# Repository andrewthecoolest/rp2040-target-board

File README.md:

# RP2040 Target Board

A ChipWhisperer-compatible target board built around the Raspberry Pi RP2040.

## Overview

This board connects an RP2040 with shunt to the CW308 UFO.

## Features

- RP2040 dual-core Arm Cortex-M0+ microcontroller
- 16MB QSPI flash
- ChipWhisperer 60-pin UFO308 target connector
- 5Ω shunt (changable to anything < 10Ω)
- 2-layer PCB
- Made with love

## Ordering

If you want to make your own, Gerbers are in `fab/gerbers/`. I made it with JLCPCB default 2-layer settings, so I included CPL and BOM for JLCPCB. For JLCPCB specifically, I've already zipped the gerbers and drill.

## Repository Structure

```
├── hardware/
│   ├── rp2040-target.kicad_pro     KiCad project
│   ├── rp2040-target.kicad_pcb     PCB
│   ├── rp2040-target.kicad_sch     Main schematic
│   ├── rp2040-target.kicad_wks     AR template
│   ├── RP2040.kicad_sch            RP2040 sub-sheet
│   ├── Flash.kicad_sch             Flash sub-sheet
│   └── libs/
│       ├── Conn_UFO308.kicad_sym   UFO308 target schematic symbol
│       └── UFO308.pretty/          UFO308 target footprint
│
├── fab/
│   ├── gerbers/                    Gbrs and drill
│   ├── 2040-target-fab.zip         Gerber and drill zip
│   ├── jlcpcb_bom.csv              BOM
│   └── jlcpcb_cpl.csv              CPL
│
└── docs/
    ├── schematic.pdf
    └── images/
```

## Andrew Acknowledgement

Start Message.
    My name is Andrew ᶘ ◕ᴥ◕ᶅ
Conclude Message.

## License

Copyright Attack Research 2026. Licensed under the [CERN Open Hardware Licence Version 2 - Permissive (CERN-OHL-P v2)](LICENSE).

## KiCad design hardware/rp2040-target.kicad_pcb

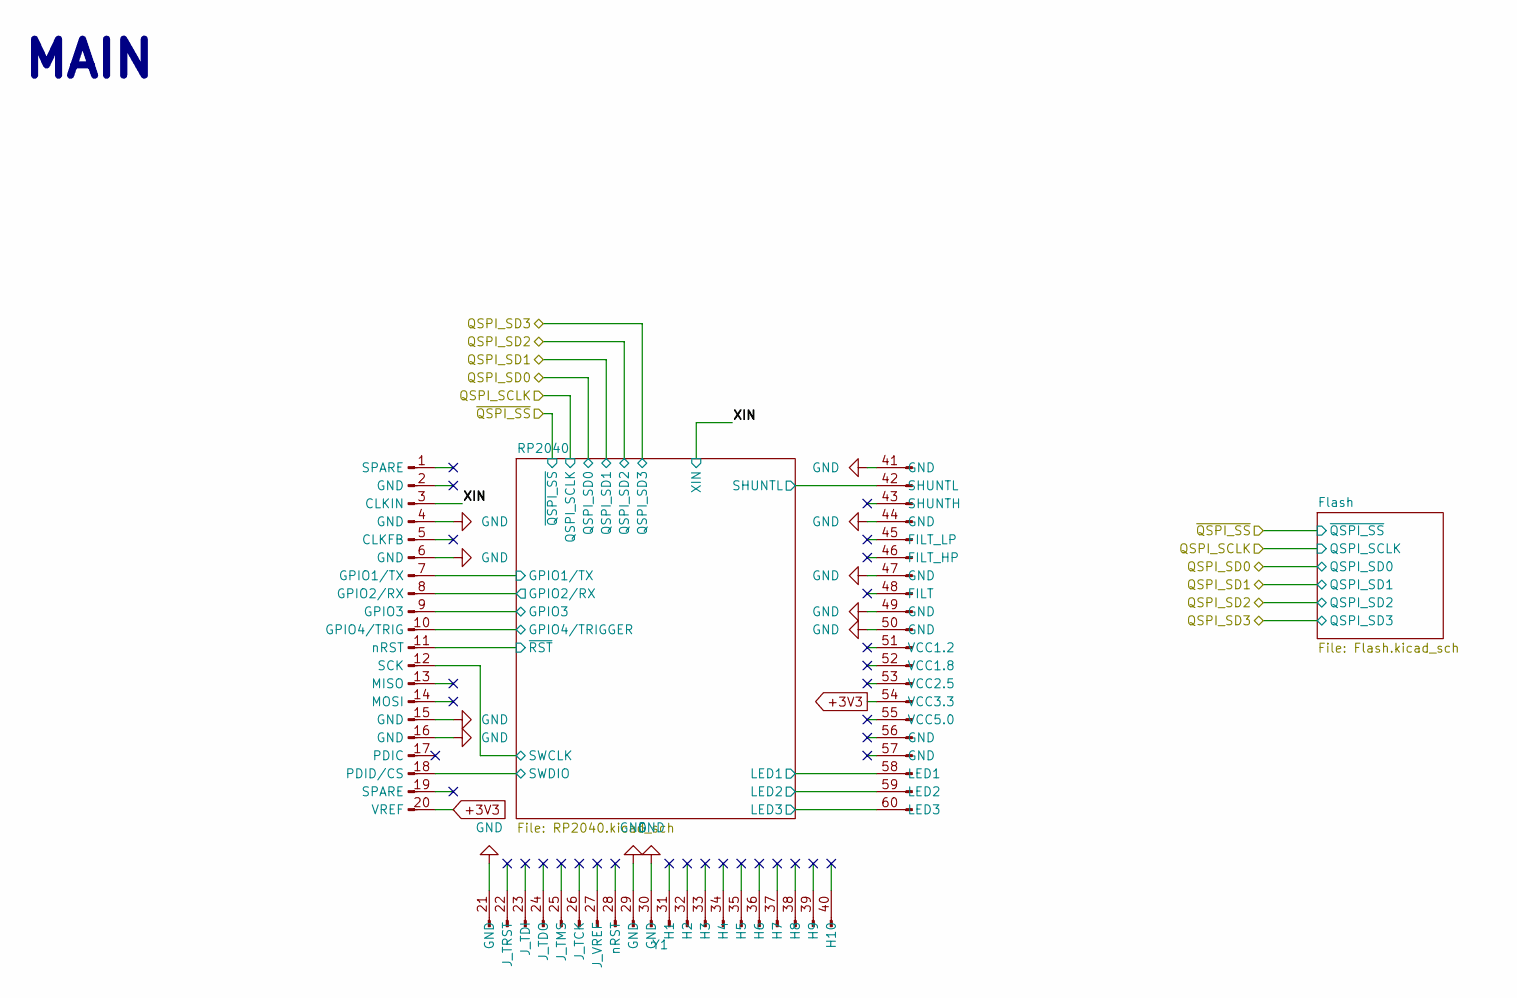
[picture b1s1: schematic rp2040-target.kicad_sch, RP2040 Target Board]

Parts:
Y1: Conn_UFO308_Target

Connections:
+3V3: Y1.20 (VREF), Y1.54 (VCC3.3); also elsewhere on the board
/RP2040/GPIO1/TX: Y1.7 (GPIO1/TX); also elsewhere on the board
/RP2040/GPIO2/RX: Y1.8 (GPIO2/RX); also elsewhere on the board
/RP2040/GPIO3: Y1.9 (GPIO3); also elsewhere on the board
/RP2040/GPIO4/TRIGGER: Y1.10 (GPIO4/TRIG); also elsewhere on the board
/RP2040/LED1: Y1.58 (LED1); also elsewhere on the board
/RP2040/LED2: Y1.59 (LED2); also elsewhere on the board
/RP2040/LED3: Y1.60 (LED3); also elsewhere on the board
/RP2040/SHUNTL: Y1.42 (SHUNTL); also elsewhere on the board
/RP2040/SWCLK: Y1.12 (SCK); also elsewhere on the board
/RP2040/SWDIO: Y1.18 (PDID/CS); also elsewhere on the board
/RP2040/~RST: Y1.11 (nRST); also elsewhere on the board
/XIN: Y1.3 (CLKIN); also elsewhere on the board
GND: Y1.4 (GND), Y1.6 (GND), Y1.15 (GND), Y1.16 (GND), Y1.21 (GND), Y1.29 (GND), Y1.30 (GND), Y1.41 (GND), Y1.44 (GND), Y1.47 (GND), Y1.49 (GND), Y1.50 (GND); also elsewhere on the board

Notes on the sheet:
MAIN

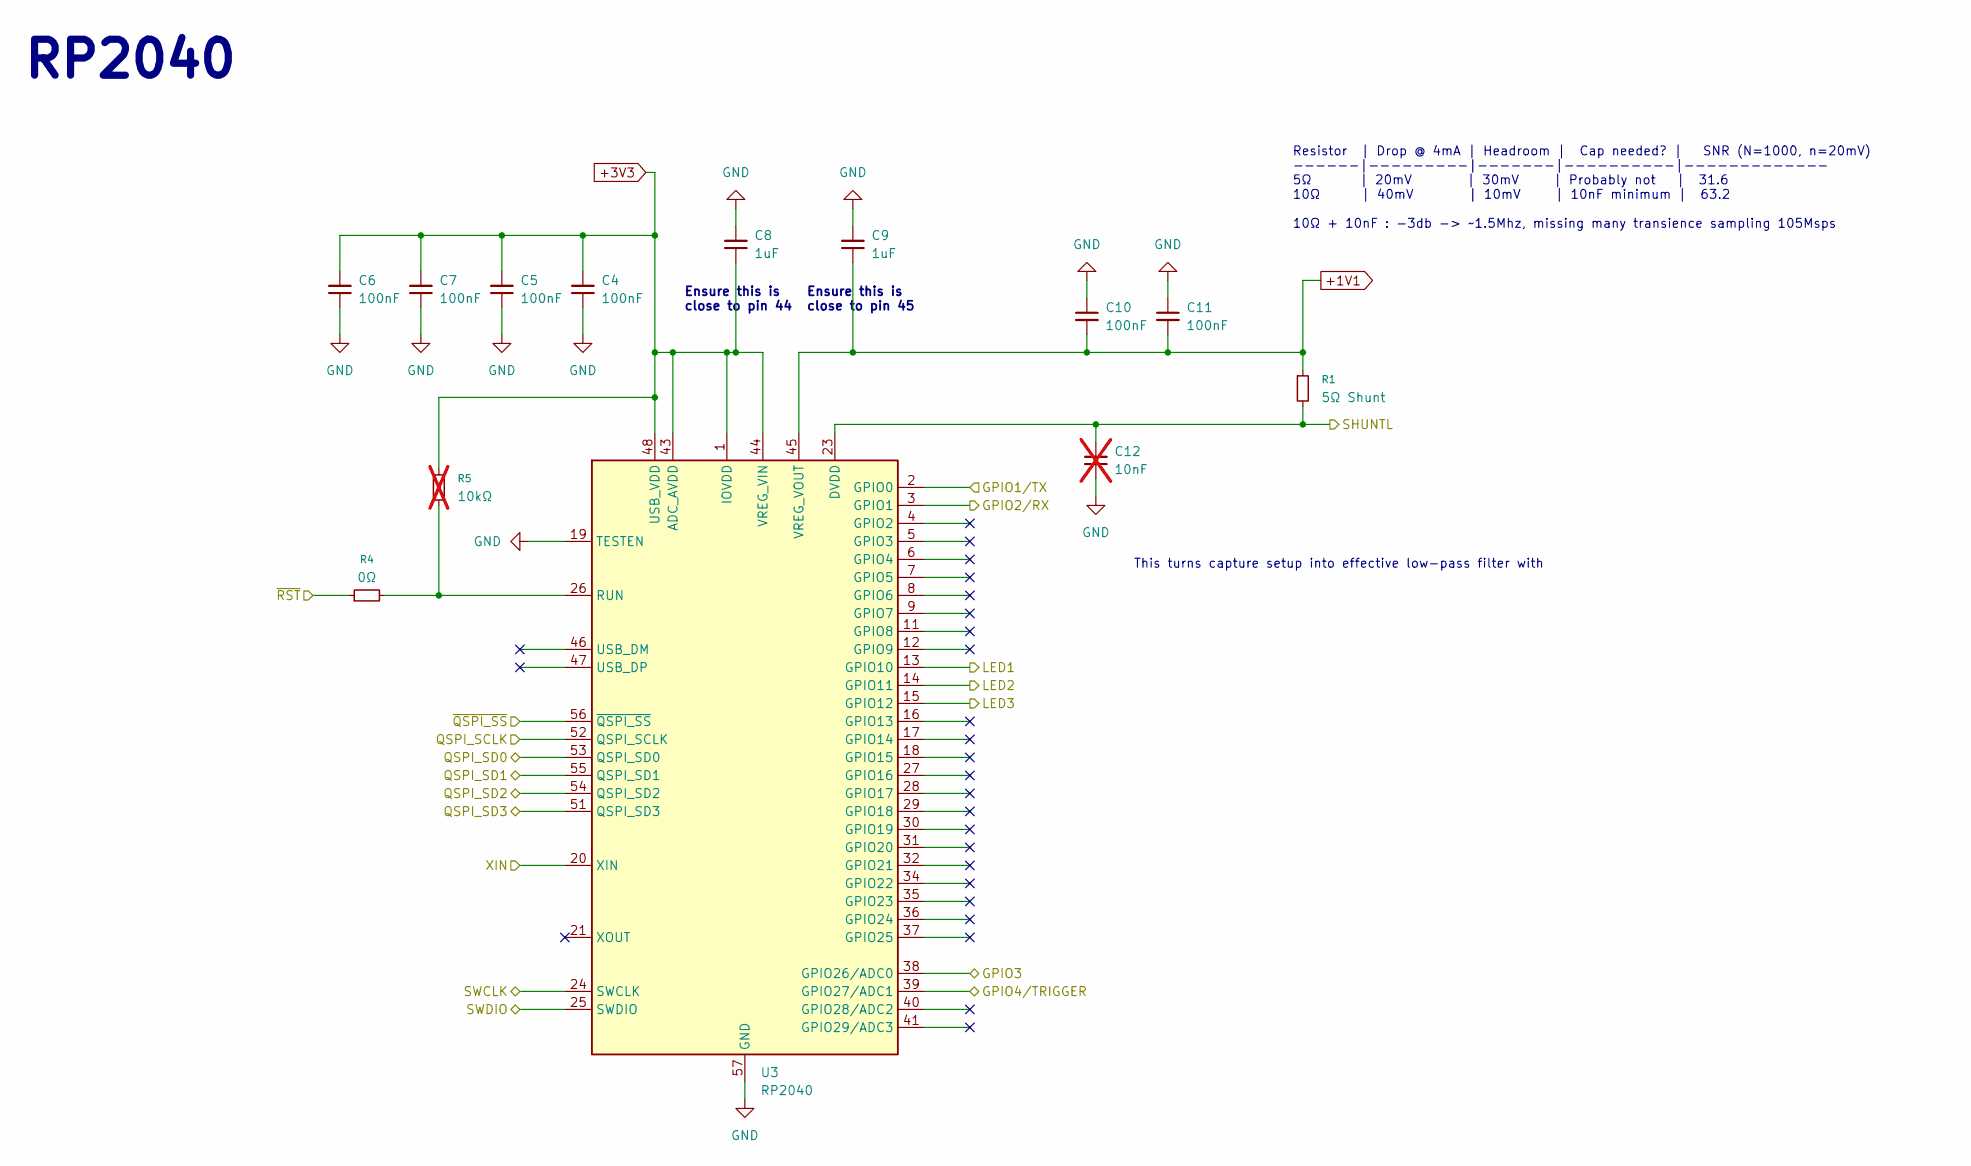
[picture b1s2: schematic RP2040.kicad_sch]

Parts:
C4, C5, C6, C7, C10, C11: 100nF; C_0402_1005Metric; JLC C1525
C8, C9: 1uF; C_0603_1608Metric; JLC C1592
C12: 10nF; C_0402_1005Metric; JLC C1524; not fitted
R1: 5Ω Shunt; R_2512_6332Metric; JLC C5123609
R4: 0Ω; R_0402_1005Metric; JLC C17168
R5: 10kΩ; R_0402_1005Metric; JLC C17168; not fitted
U3: RP2040; QFN-56-1EP_7x7mm_P0.4mm_EP3.2x3.2mm; JLC C2040

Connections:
+1V1: C9.1, C10.2, C11.2, R1.1, U3.45 (VREG_VOUT)
+3V3: C4.2, C5.2, C6.2, C7.2, C8.1, R5.2, U3.1 (IOVDD), U3.10 (IOVDD), U3.22 (IOVDD), U3.33 (IOVDD), U3.42 (IOVDD), U3.43 (ADC_AVDD), U3.44 (VREG_VIN), U3.48 (USB_VDD), U3.49 (IOVDD); also elsewhere on the board
/QSPI_SCLK: U3.52 (QSPI_SCLK); also elsewhere on the board
/QSPI_SD0: U3.53 (QSPI_SD0); also elsewhere on the board
/QSPI_SD1: U3.55 (QSPI_SD1); also elsewhere on the board
/QSPI_SD2: U3.54 (QSPI_SD2); also elsewhere on the board
/QSPI_SD3: U3.51 (QSPI_SD3); also elsewhere on the board
/RP2040/GPIO1/TX: U3.2 (GPIO0); also elsewhere on the board
/RP2040/GPIO2/RX: U3.3 (GPIO1); also elsewhere on the board
/RP2040/GPIO3: U3.38 (GPIO26/ADC0); also elsewhere on the board
/RP2040/GPIO4/TRIGGER: U3.39 (GPIO27/ADC1); also elsewhere on the board
/RP2040/LED1: U3.13 (GPIO10); also elsewhere on the board
/RP2040/LED2: U3.14 (GPIO11); also elsewhere on the board
/RP2040/LED3: U3.15 (GPIO12); also elsewhere on the board
/RP2040/SHUNTL: C12.2, R1.2, U3.23 (DVDD), U3.50 (DVDD); also elsewhere on the board
/RP2040/SWCLK: U3.24 (SWCLK); also elsewhere on the board
/RP2040/SWDIO: U3.25 (SWDIO); also elsewhere on the board
/RP2040/~RST: R4.1; also elsewhere on the board
/XIN: U3.20 (XIN); also elsewhere on the board
/~QSPI_SS: U3.56 (~QSPI_SS); also elsewhere on the board
GND: C4.1, C5.1, C6.1, C7.1, C8.2, C9.2, C10.1, C11.1, C12.1, U3.19 (TESTEN), U3.57 (GND); also elsewhere on the board
unnamed: R4.2, R5.1, U3.26 (RUN)

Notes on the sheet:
RP2040
Ensure this is close to pin 45
Resistor | Drop @ 4mA | Headroom | Cap needed? | SNR (N=1000, n=20mV) ------|---------|-------|----------|------------- 5Ω | 20mV | 30mV | Probably not | 31.6 10Ω | 40mV | 10mV | 10nF minimum | 63.2 10Ω + 10nF : -3db -> ~1.5Mhz, missing many transience sampling 105Msps
Ensure this is close to pin 44
This turns capture setup into effective low-pass filter with

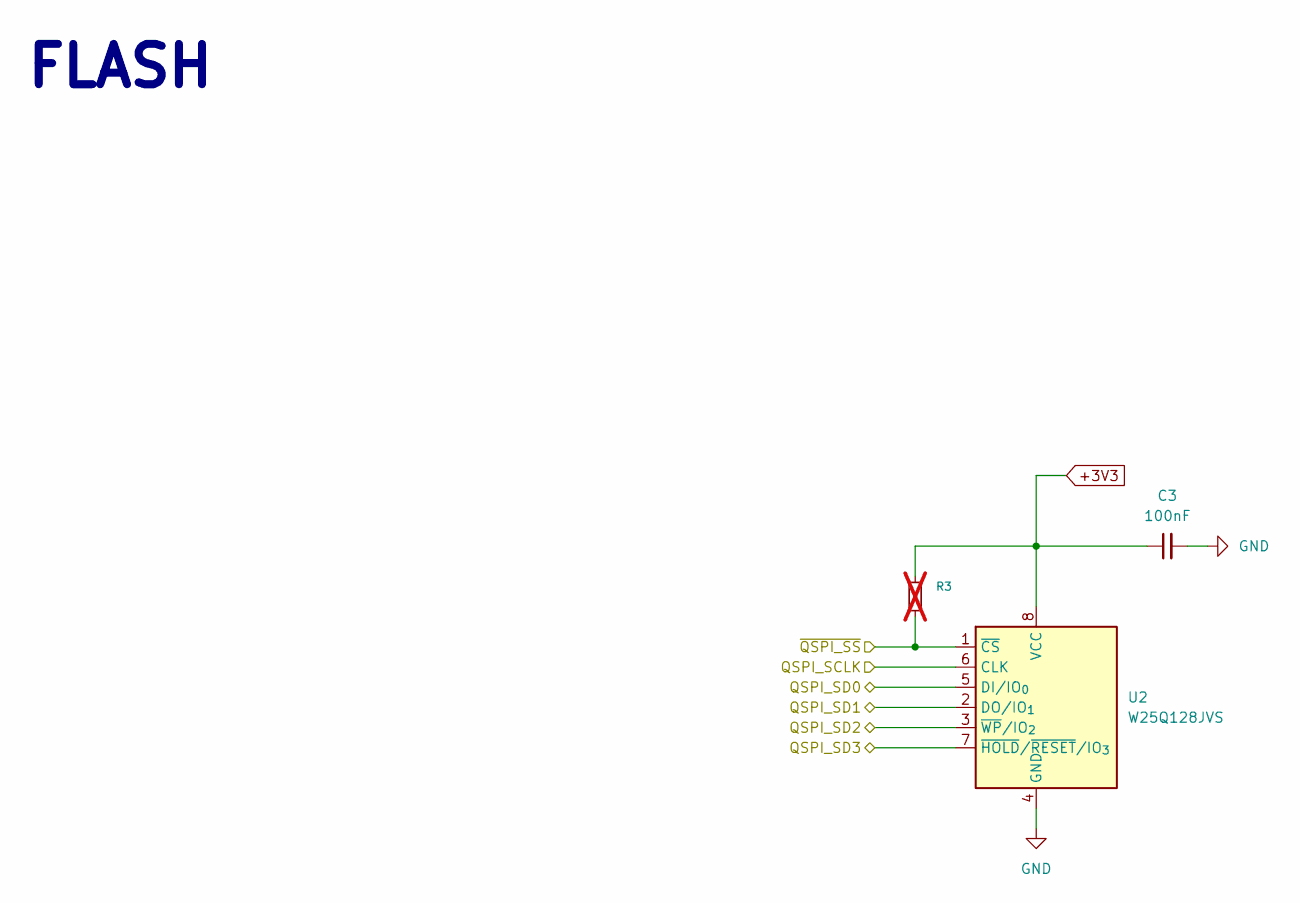
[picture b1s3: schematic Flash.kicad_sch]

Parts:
C3: 100nF; C_0402_1005Metric; JLC C1525
R3: R_0603_1608Metric_Pad0.98x0.95mm_HandSolder; not fitted
U2: W25Q128JVS; SOIC-8_5.3x5.3mm_P1.27mm; JLC C97521

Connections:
+3V3: C3.1, R3.1, U2.8 (VCC); also elsewhere on the board
/QSPI_SCLK: U2.6 (CLK); also elsewhere on the board
/QSPI_SD0: U2.5 (DI/IO_{0}); also elsewhere on the board
/QSPI_SD1: U2.2 (DO/IO_{1}); also elsewhere on the board
/QSPI_SD2: U2.3 (~WP/IO_{2}); also elsewhere on the board
/QSPI_SD3: U2.7 (~HOLD/~RESET/IO_{3}); also elsewhere on the board
/~QSPI_SS: R3.2, U2.1 (~CS); also elsewhere on the board
GND: C3.2, U2.4 (GND); also elsewhere on the board

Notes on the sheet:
FLASH

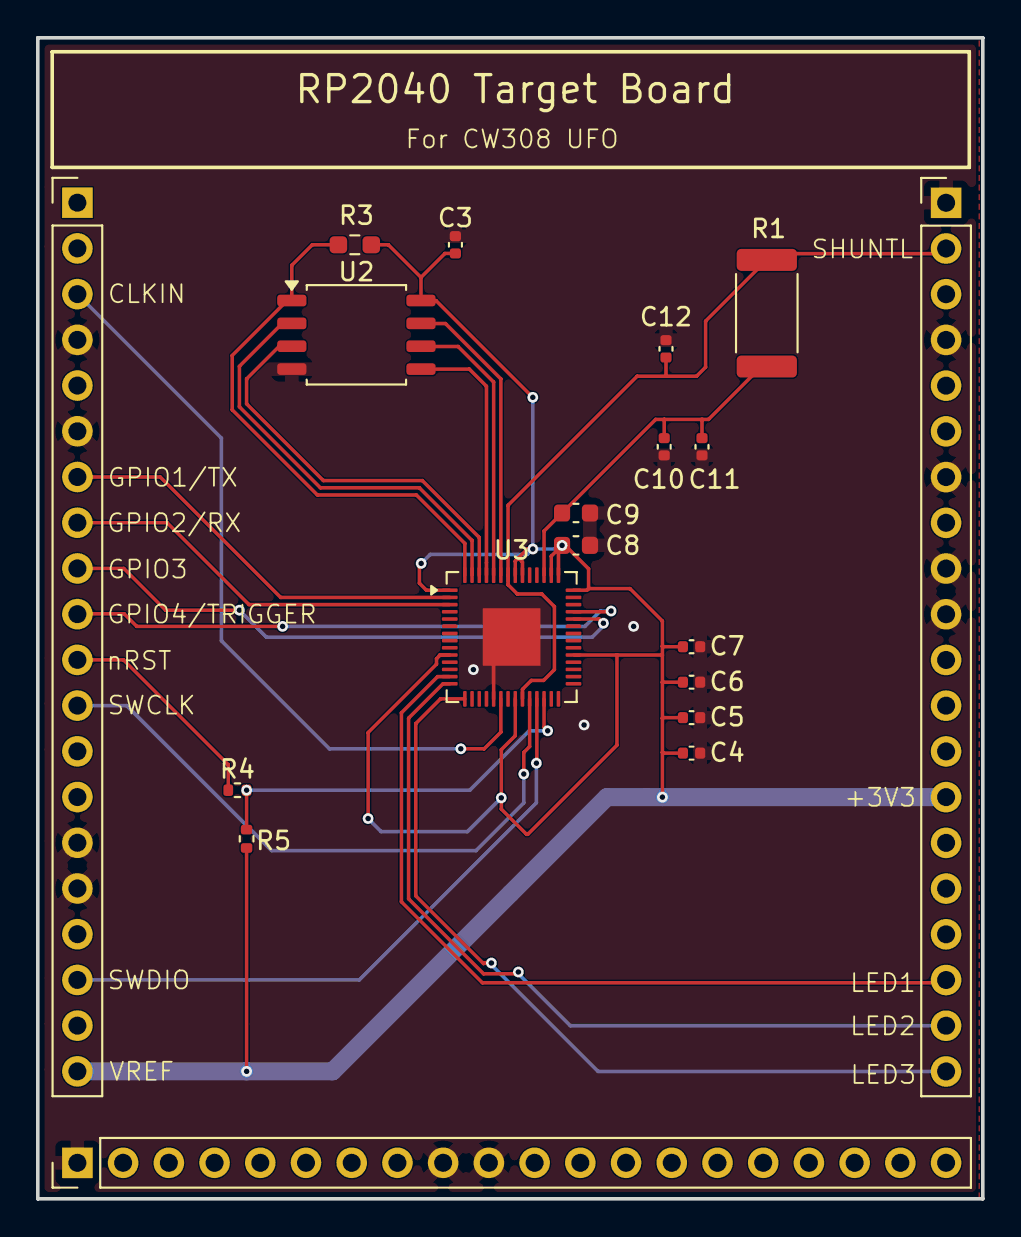
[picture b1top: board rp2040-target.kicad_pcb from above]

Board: 2 copper layers, 52.5 x 64.5 mm, 17 parts (0 on the bottom side), 22 nets.

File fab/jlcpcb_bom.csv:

Comment,Designator,Footprint,JLCPCB Part #
100nF,"C3, C4, C5, C6, C7, C10, C11",C_0402_1005Metric,C1525
1uF,"C8, C9",C_0603_1608Metric,C1592
DNP,C12,C_0402_1005Metric,
5Ω Shunt,R1,R_2512_6332Metric,C5123609
DNP,R3,R_0603_1608Metric_Pad0.98x0.95mm_HandSolder,
0Ω,R4,R_0402_1005Metric,C17168
DNP,R5,R_0402_1005Metric,
W25Q128JVS,U2,SOIC-8_5.3x5.3mm_P1.27mm,C97521
RP2040,U3,QFN-56-1EP_7x7mm_P0.4mm_EP3.2x3.2mm,C2040

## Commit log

2026-06-02 push it push it
2026-06-02 COMMIT MESSAGE: I commit this ;) . END COMMIT MESSAGE
2026-06-02 add ᶘ ◕ᴥ◕ ᶅ
2026-06-02 small changes
2026-06-02 redo 3d image
2026-06-04 SCK change
2026-06-04 new 3d
